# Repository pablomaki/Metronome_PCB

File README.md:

# Metronome_PCB

| ❗ NOTE          |
|:---------------------------|
| This design is still work in process. PCB has been confirmed to work on breadboard, but actual PCB is still in mail. After the PCB has been confirmed to be functioning properly, I will add BOM and design an enclosure for it. |

## Description

This metronome PCB is based on a simple 555 oscillator producing frequency adjustable square wave with 0.5 dutycycle. In addition the board contains CD4017BE counter circuit that can be used to drive two separate LEDs so that one flashes either every 2, 3 or 4 beats while the other flashes on every beat. The length of a bar can be chosen by separate switch or just hardwired for specific one.

The metronome works with supply voltage of 5 to 15 V, 9V battery is recommended and works well for this purpose. Note that the voltage used may affect the loudness of the speaker. Loudness can also be affected by a separate volume resistor.

## BOM

TO BE ADDED

## Enclosure

TO BE ADDED

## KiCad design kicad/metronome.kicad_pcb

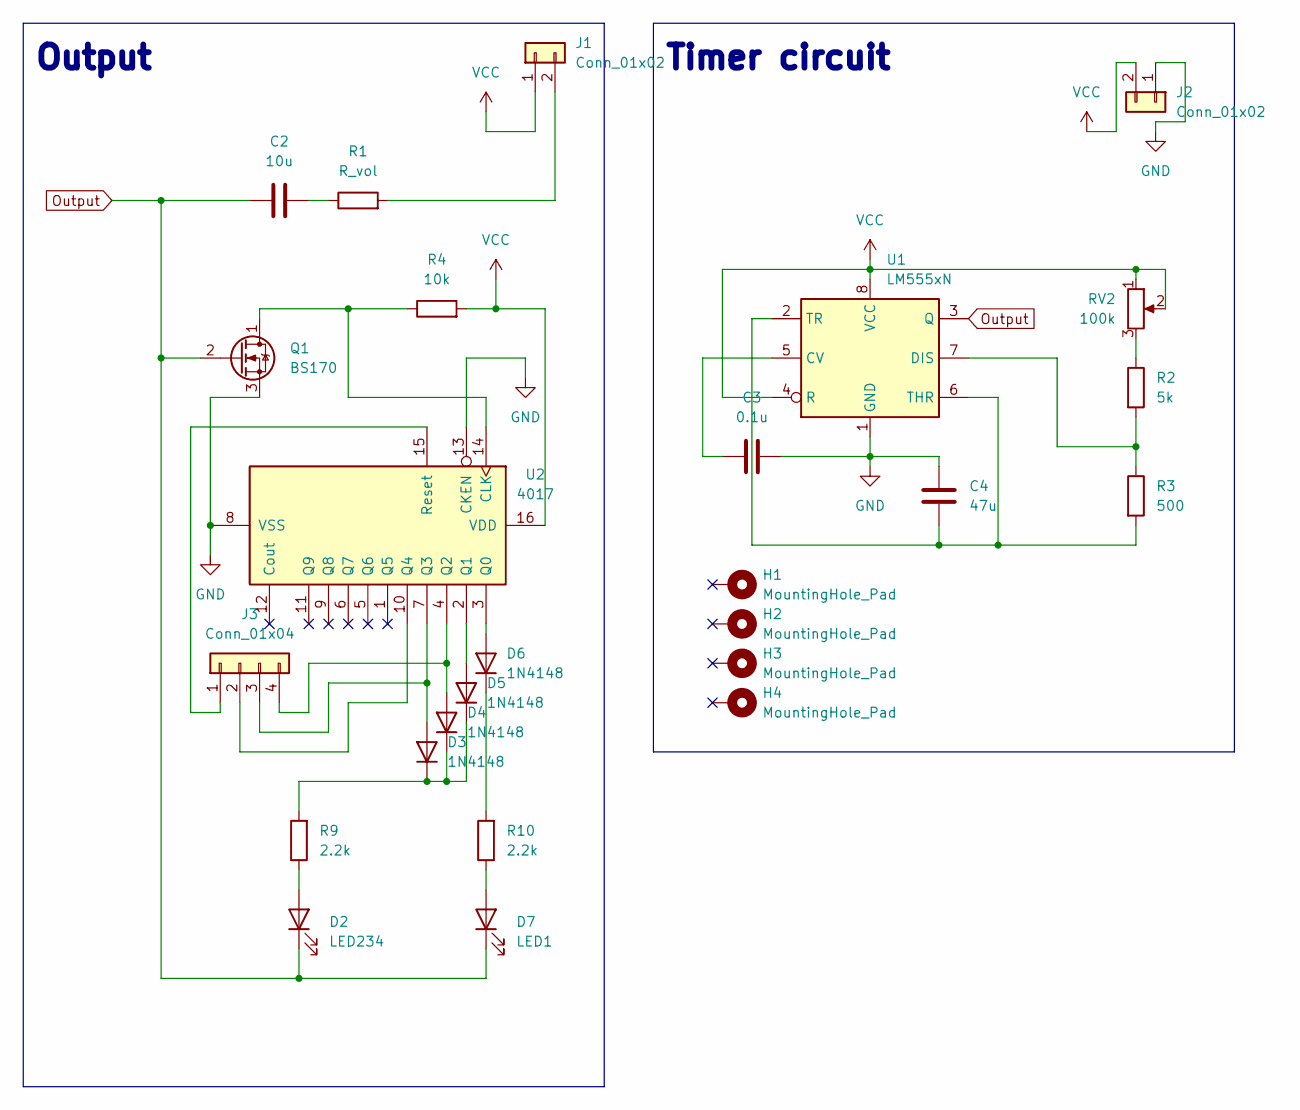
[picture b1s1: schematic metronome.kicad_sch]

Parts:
C2: 10u; C_Radial_D5.0mm_H11.0mm_P2.00mm
C3: 0.1u; C_Radial_D5.0mm_H11.0mm_P2.00mm
C4: 47u; C_Radial_D6.3mm_H11.0mm_P2.50mm
D2: LED234; LED_D5.0mm
D3, D4, D5, D6: 1N4148; D_DO-35_SOD27_P7.62mm_Horizontal
D7: LED1; LED_D5.0mm
H1, H2, H3, H4: MountingHole_Pad; MountingHole_3.2mm_M3_ISO7380_Pad
J1, J2: Conn_01x02; JST_XH_B2B-XH-A_1x02_P2.50mm_Vertical
J3: Conn_01x04; JST_XH_B4B-XH-A_1x04_P2.50mm_Vertical
Q1: BS170; TO-92_Inline
R1: R_vol; R_Axial_DIN0207_L6.3mm_D2.5mm_P10.16mm_Horizontal
R2: 5k; R_Axial_DIN0207_L6.3mm_D2.5mm_P10.16mm_Horizontal
R3: 500; R_Axial_DIN0207_L6.3mm_D2.5mm_P10.16mm_Horizontal
R4: 10k; R_Axial_DIN0207_L6.3mm_D2.5mm_P10.16mm_Horizontal
R9, R10: 2.2k; R_Axial_DIN0207_L6.3mm_D2.5mm_P10.16mm_Horizontal
RV2: 100k; JST_XH_B3B-XH-A_1x03_P2.50mm_Vertical
U1: LM555xN; DIP-8_W7.62mm
U2: 4017; DIP-16_W7.62mm

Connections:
GND: C3.1, C4.1, J2.1, Q1.3 (S), U1.1 (GND), U2.8 (VSS), U2.13 (CKEN)
unnamed: C2.2, R1.1
unnamed: C3.2, U1.5 (CV)
unnamed: C4.2, R3.2, U1.2 (TR), U1.6 (THR)
unnamed: D2.2 (A), R9.1
unnamed: D3.1 (K), D4.1 (K), D5.1 (K), R9.2
unnamed: D3.2 (A), J3.3, U2.7 (Q3)
unnamed: D4.2 (A), J3.4, U2.4 (Q2)
unnamed: D5.2 (A), U2.2 (Q1)
unnamed: D6.1 (K), R10.2
unnamed: D6.2 (A), U2.3 (Q0)
unnamed: D7.2 (A), R10.1
unnamed: J1.2, R1.2
unnamed: Q1.1 (D), R4.1, U2.14 (CLK)
unnamed: R2.1, RV2.3
unnamed: R2.2, R3.1, U1.7 (DIS)
unnamed: J3.2, U2.10 (Q4)
unnamed: J3.1, U2.15 (Reset)
Output: C2.1, D2.1 (K), D7.1 (K), Q1.2 (G), U1.3 (Q)
VCC: J1.1, J2.2, R4.2, RV2.1, RV2.2, U1.4 (R), U1.8 (VCC), U2.16 (VDD)

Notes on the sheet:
Output
Timer circuit

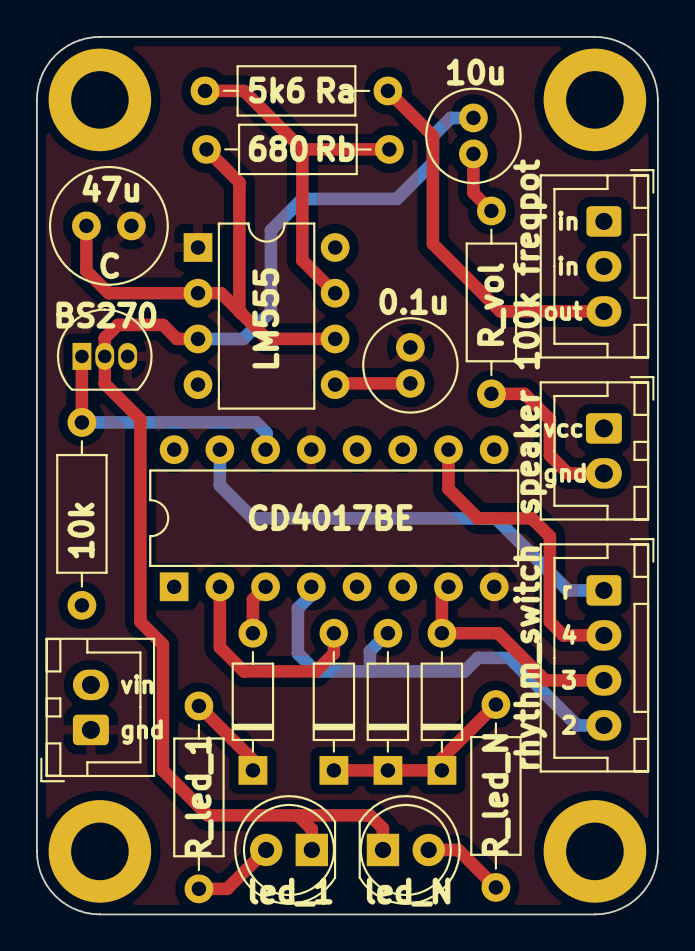
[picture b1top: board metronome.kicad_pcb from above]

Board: 2 copper layers, 34.5 x 48.8 mm, 26 parts (0 on the bottom side), 20 nets.

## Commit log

2023-05-18 Initial push
2023-05-23 Update gerber files
2025-01-17 Add PCB .step file
